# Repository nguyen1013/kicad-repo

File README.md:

# KiCad Practice Repository

This repository contains my practice projects for KiCad and QSPICE. It will be updated in the future to include:
-   Library collections    
-   PCB designs  

Feel free to explore and contribute!

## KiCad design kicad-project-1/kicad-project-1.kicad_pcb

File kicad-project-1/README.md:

# Kicad - Project 1

## Description:
- Single-sided circuit board . 
- 0.5 mm clearance
- 0.5 mm signal width
- Functional blocks marked in the schematic picture
- PCB size 100 mm x 80 mm
- The connectors are 2.54 mm (pin spacing) vertical row connectors

## The schematic and 3D view:

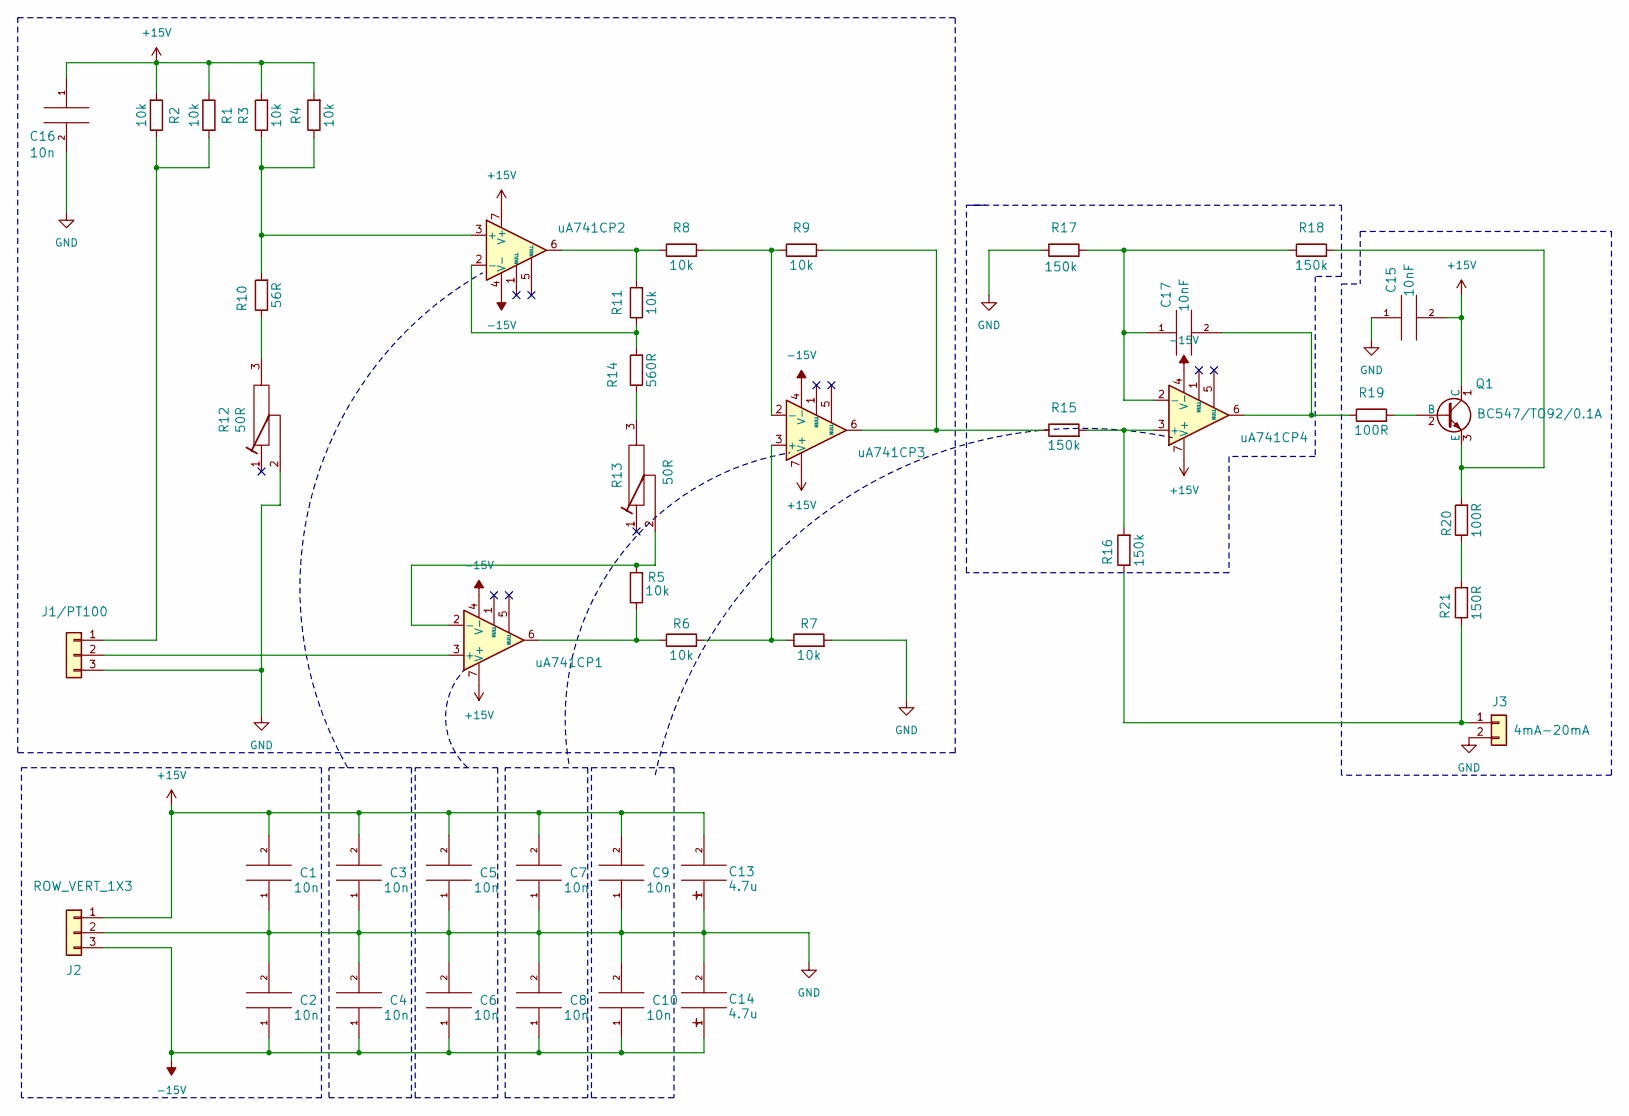
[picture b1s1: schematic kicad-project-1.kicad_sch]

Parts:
C1, C2, C3, C4, C5, C6, C7, C8, C9, C10: 10n; C5_0; Tolerance +-10%
C13, C14: 4.7u; C_P_2_0_5; Tolerance +-20%
C15, C16, C17: 10nF; C5_0; Tolerance +-10%
J1/PT100, J2: ROW_VERT_1X3; ROW_VERT_1x3
J3: 4mA-20mA; ROW_VERT_1x2
Q1: BC547/TO92/0.1A; TO-92
R1, R2, R3, R4, R5, R6, R7, R8, R9, R11: 10k; R3_5W; Tolerance +-1%
R10: 56R; R3_5W; Tolerance +-1%
R12, R13: 50R; TRIMMER
R14: 560R; R3_5W; Tolerance +-1%
R15, R16, R17, R18: 150k; R3_5W; Tolerance +-1%
R19, R20: 100R; R3_5W; Tolerance +-1%
R21: 150R; R3_5W; Tolerance +-1%
uA741CP1, uA741CP2, uA741CP3, uA741CP4: uA741CP_DIL8; DIL8

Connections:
+15V: C1.2, C3.2, C5.2, C7.2, C9.2, C13.2, C15.2, C16.1, J2.1, Q1.1 (C), R1.2, R2.2, R3.2, R4.2, uA741CP1.7 (V+), uA741CP2.7 (V+), uA741CP3.7 (V+), uA741CP4.7 (V+)
-15V: C2.1, C4.1, C6.1, C8.1, C10.1, C14.1, J2.3, uA741CP1.4 (V-), uA741CP2.4 (V-), uA741CP3.4 (V-), uA741CP4.4 (V-)
GND: C1.1, C2.2, C3.1, C4.2, C5.1, C6.2, C7.1, C8.2, C9.1, C10.2, C13.1, C14.2, C15.1, C16.2, J1/PT100.3, J2.2, J3.2, R7.2, R12.2, R17.2
unnamed: C17.2, R19.1, uA741CP4.6
unnamed: J1/PT100.1, R1.1, R2.1
unnamed: J1/PT100.2, uA741CP1.3 (+)
unnamed: J3.1, R16.1, R21.1
unnamed: Q1.2 (B), R19.2
unnamed: Q1.3 (E), R18.2, R20.2
unnamed: R5.1, R6.1, uA741CP1.6
unnamed: R10.1, R12.3
unnamed: R8.1, R11.2, uA741CP2.6
unnamed: R13.3, R14.1
unnamed: R9.2, R15.1, uA741CP3.6
unnamed: R20.1, R21.2
unnamed: R5.2, R13.2, uA741CP1.2 (-)
unnamed: R3.1, R4.1, R10.2, uA741CP2.3 (+)
unnamed: R11.1, R14.2, uA741CP2.2 (-)
unnamed: R6.2, R7.1, uA741CP3.3 (+)
unnamed: R8.2, R9.1, uA741CP3.2 (-)
unnamed: R15.2, R16.2, uA741CP4.3 (+)
unnamed: C17.1, R17.1, R18.1, uA741CP4.2 (-)

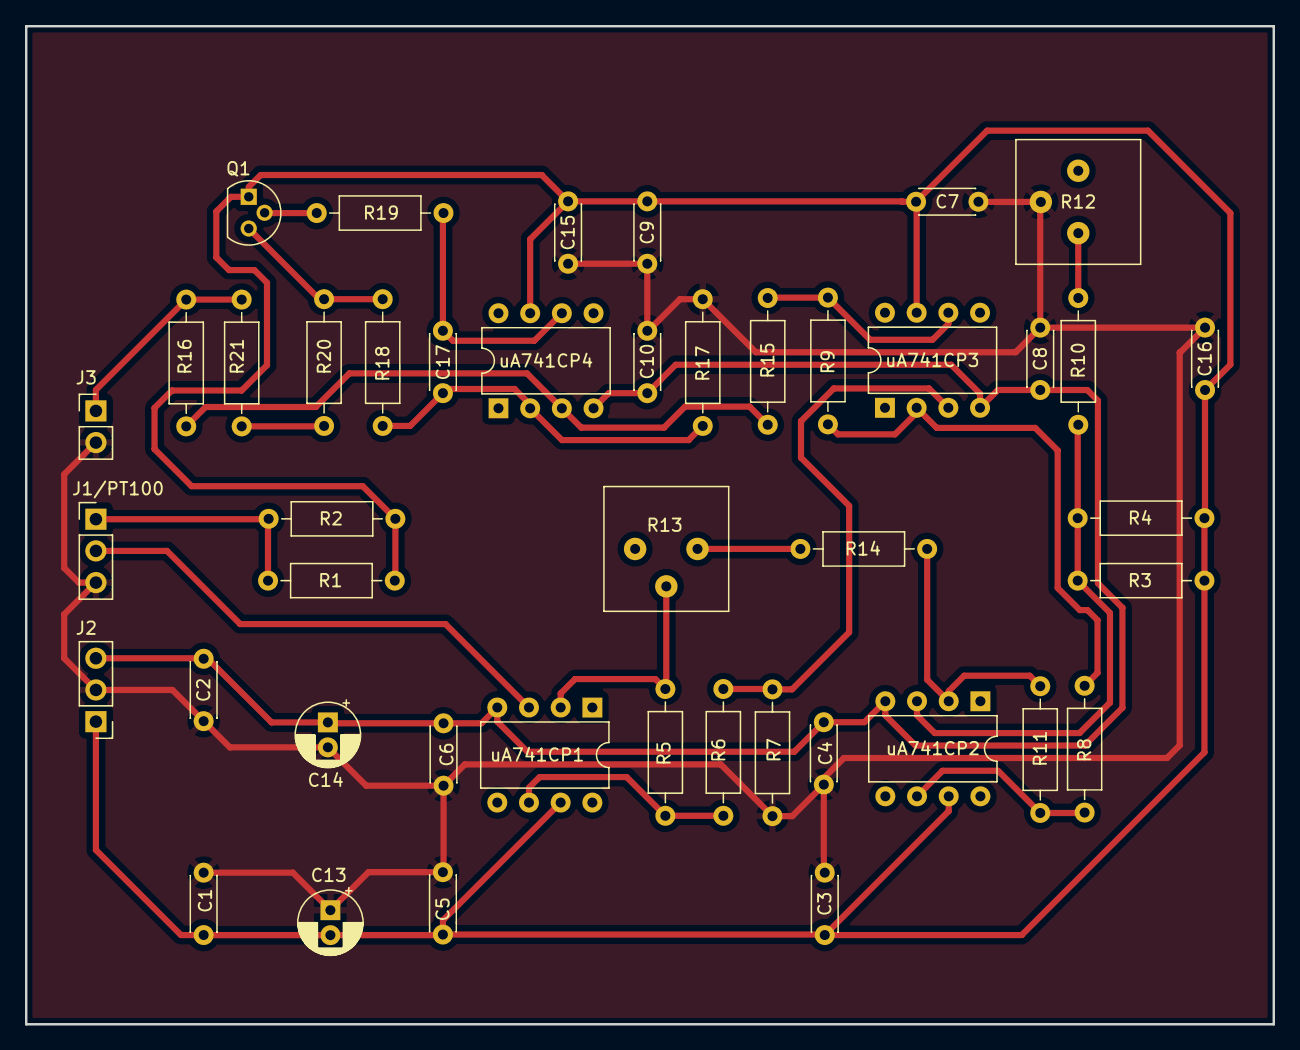
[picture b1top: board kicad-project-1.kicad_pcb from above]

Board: 2 copper layers, 100.0 x 80.0 mm, 44 parts (0 on the bottom side), 22 nets.

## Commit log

2025-01-03 add project 1
2025-01-03 add README
2025-01-03 update README project 1
